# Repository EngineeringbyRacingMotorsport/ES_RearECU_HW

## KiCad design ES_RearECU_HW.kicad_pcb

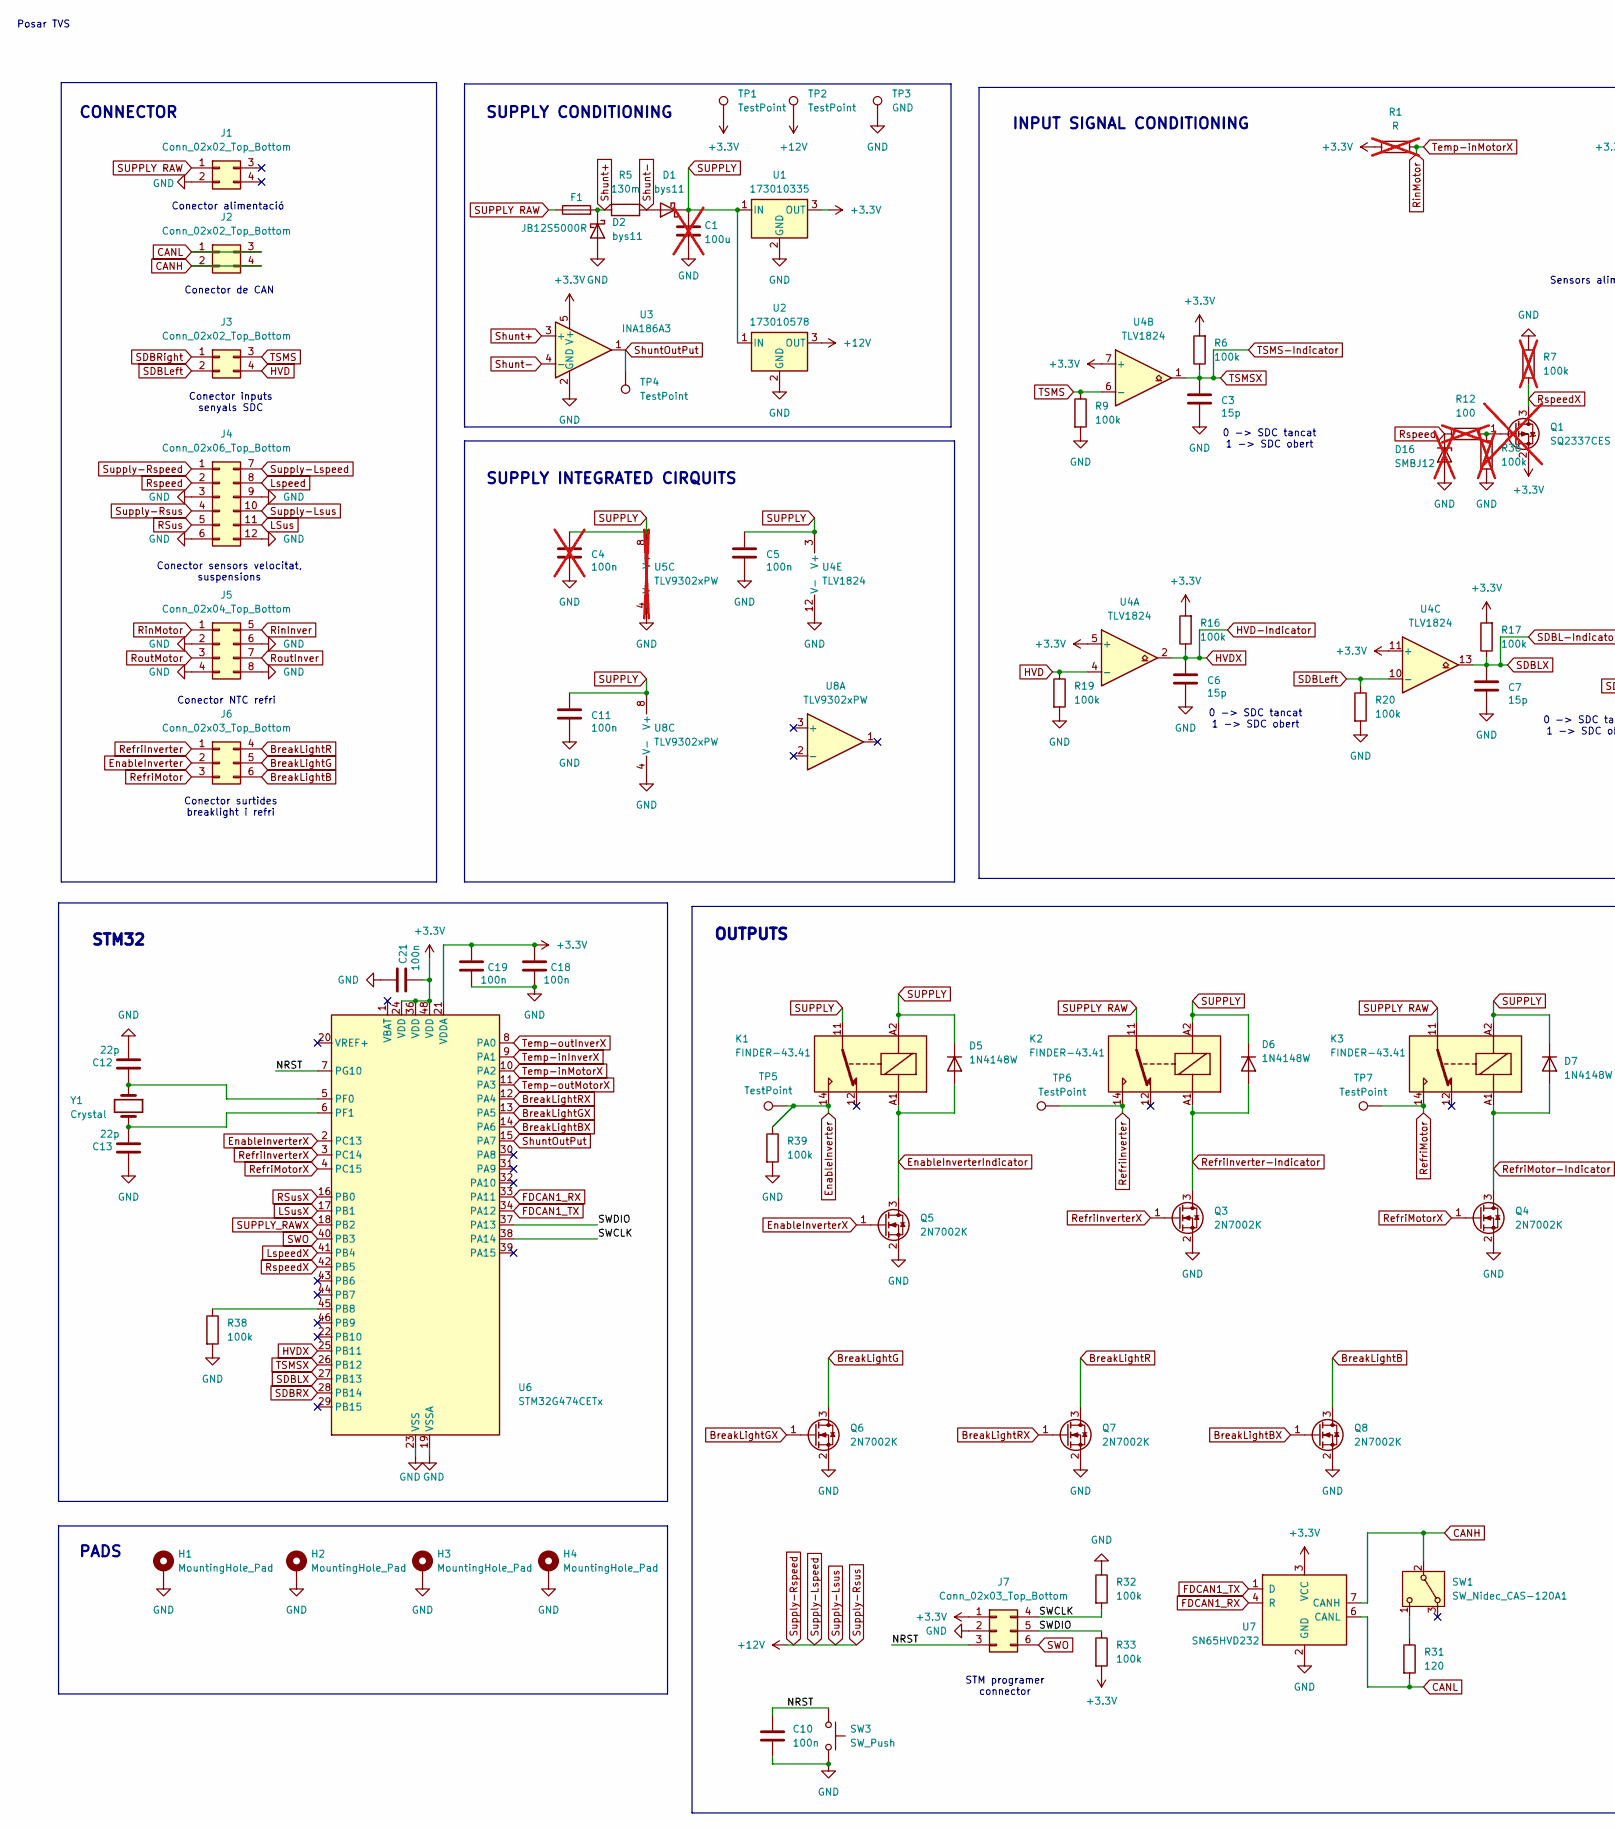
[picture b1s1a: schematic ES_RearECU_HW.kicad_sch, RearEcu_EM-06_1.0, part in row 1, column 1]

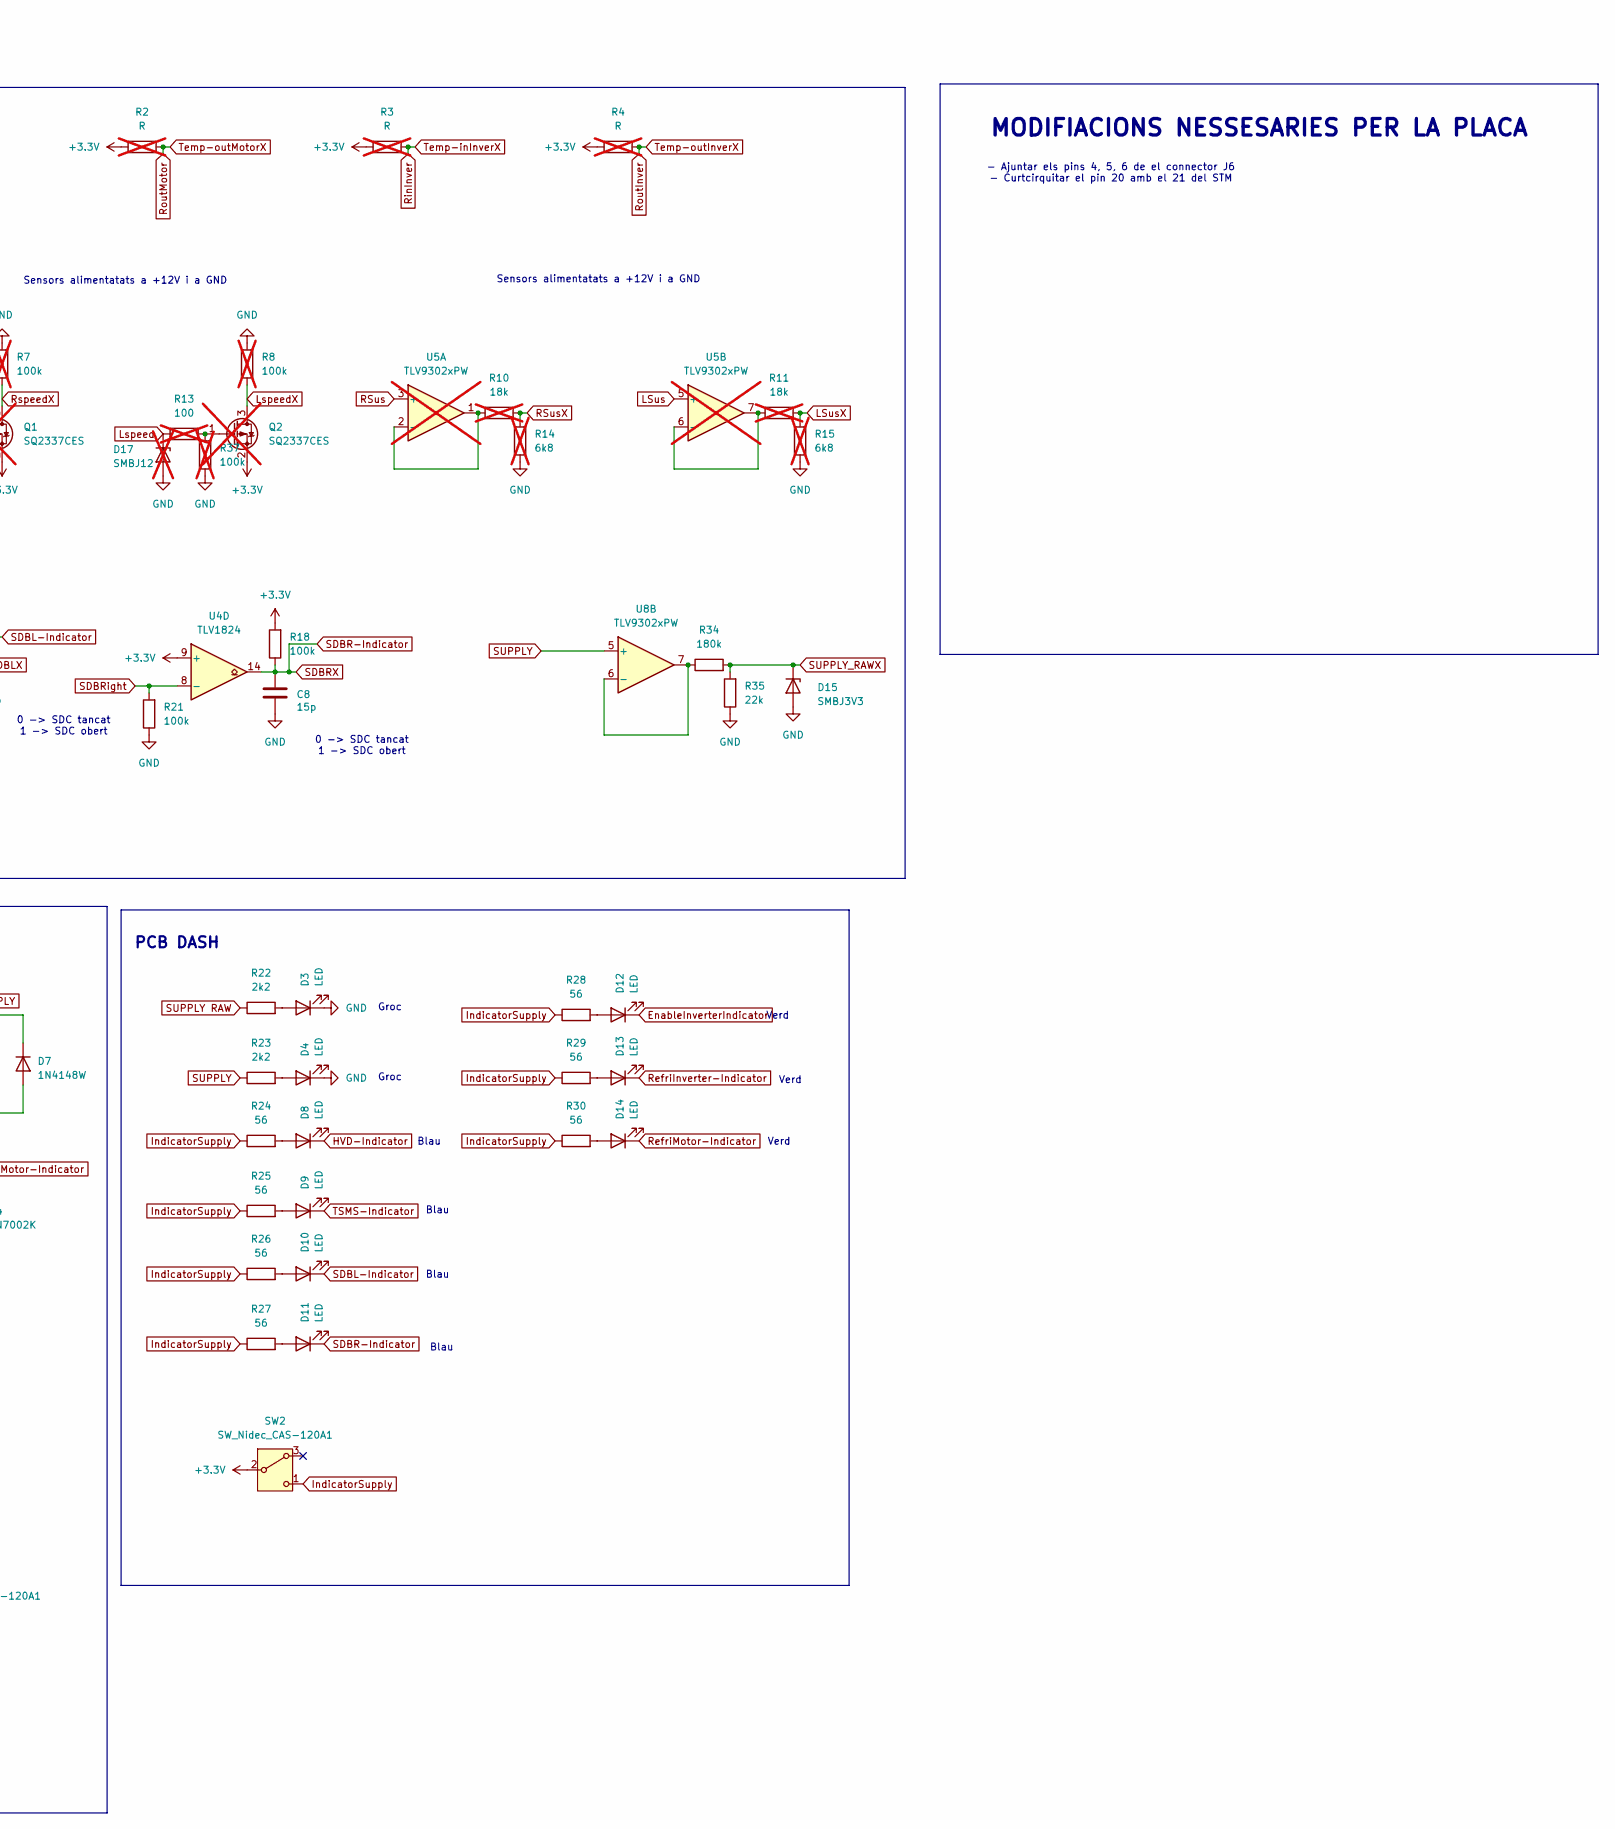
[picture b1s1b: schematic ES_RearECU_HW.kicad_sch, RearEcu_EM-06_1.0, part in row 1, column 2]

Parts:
C1: 100u; CP_Elec_10x10; not fitted
C3, C6, C7, C8: 15p; C_1206_3216Metric
C4: 100n; C_1206_3216Metric; not fitted
C5, C10, C11, C18, C19, C21: 100n; C_1206_3216Metric
C12, C13: 22p; C_1206_3216Metric
D1, D2: bys11; D_SMA
D3, D4, D8, D9, D10, D11, D12, D13, D14: LED; LED_0603_1608Metric
D5, D6, D7: 1N4148W; D_SOD-123
D15: SMBJ3V3; D_SMB
D16, D17: SMBJ12; D_SMB; not fitted
F1: JB12S5000R; Fuse_1206_3216Metric
H1, H2, H3, H4: MountingHole_Pad; MountingHole_3.5mm_Pad_Via
J1, J2, J3: Conn_02x02_Top_Bottom; Molex_Nano-Fit_105314-xx04_2x02_P2.50mm_Horizontal
J4: Conn_02x06_Top_Bottom; Molex_Nano-Fit_105314-xx12_2x06_P2.50mm_Horizontal
J5: Conn_02x04_Top_Bottom; Molex_Nano-Fit_105314-xx08_2x04_P2.50mm_Horizontal
J6: Conn_02x03_Top_Bottom; Molex_Nano-Fit_105314-xx06_2x03_P2.50mm_Horizontal
J7: Conn_02x03_Top_Bottom; Molex_Nano-Fit_105310-xx06_2x03_P2.50mm_Vertical
K1, K2, K3: FINDER-43.41; FINDER434170242001
Q1, Q2: SQ2337CES; SOT-23; not fitted
Q3, Q4, Q5, Q6, Q7, Q8: 2N7002K; SOT-23
R1, R2, R3, R4: R; R_1206_3216Metric; not fitted
R5: 130m; R_1206_3216Metric
R6, R9, R16, R17, R18, R19, R20, R21, R32, R33, R38, R39: 100k; R_1206_3216Metric
R7, R8, R36, R37: 100k; R_1206_3216Metric; not fitted
R10, R11: 18k; R_1206_3216Metric; not fitted
R12, R13: 100; R_1206_3216Metric; not fitted
R14, R15: 6k8; R_1206_3216Metric; not fitted
R22, R23: 2k2; R_1206_3216Metric
R24, R25, R26, R27, R28, R29, R30: 56; R_1206_3216Metric
R31: 120; R_1206_3216Metric
R34: 180k; R_1206_3216Metric
R35: 22k; R_1206_3216Metric
SW1, SW2: SW_Nidec_CAS-120A1; Nidec_Copal_CAS-120A
SW3: SW_Push; SW_Tactile_Straight_KSA0Axx1LFTR
TP1, TP2, TP4, TP5, TP6, TP7: TestPoint; TestPoint_Pad_D1.0mm
TP3: GND; TestPoint_Pad_D1.0mm
U1: 173010335; Converter_DCDC_RECOM_R-78E-0.5_THT
U2: 173010578; Converter_DCDC_RECOM_R-78E-0.5_THT
U3: INA186A3; SOT-23-5
U4: TLV1824; TSSOP-14_4.4x5mm_P0.65mm
U5: TLV9302xPW; TSSOP-8_4.4x3mm_P0.65mm; not fitted
U6: STM32G474CETx; LQFP-48_7x7mm_P0.5mm
U7: SN65HVD232; SOIC-8_3.9x4.9mm_P1.27mm
U8: TLV9302xPW; TSSOP-8_4.4x3mm_P0.65mm
Y1: Crystal; Crystal_SMD_HC49-SD

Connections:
+3.3V: C18.1, C19.1, C21.2, J7.1, Q1.2 (S), Q2.2 (S), R1.1, R2.1, R3.1, R4.1, R6.2, R16.2, R17.2, R18.2, R33.2, SW2.2 (B), TP1.1, U1.3 (OUT), U3.5 (V+), U4.5 (+), U4.7 (+), U4.9 (+), U4.11 (+), U6.21 (VDDA), U6.24 (VDD), U6.36 (VDD), U6.48 (VDD), U7.3 (VCC)
/NRST: C10.1, J7.3, SW3.1, U6.7 (PG10)
/SWCLK: J7.4, R32.2, U6.38 (PA14)
/SWDIO: J7.5, R33.1, U6.37 (PA13)
BreakLightB: J6.6, Q8.3 (D)
BreakLightBX: Q8.1 (G), U6.14 (PA6)
BreakLightG: J6.5, Q6.3 (D)
BreakLightGX: Q6.1 (G), U6.13 (PA5)
BreakLightR: J6.4, Q7.3 (D)
BreakLightRX: Q7.1 (G), U6.12 (PA4)
CANH: J2.2, J2.4, SW1.2 (B), U7.7 (CANH)
CANL: J2.1, J2.3, R31.2, U7.6 (CANL)
EnableInverter: J6.2, K1.14, R39.1, TP5.1
EnableInverterIndicator: D5.2 (A), D12.1 (K), K1.A1, Q5.3 (D)
EnableInverterX: Q5.1 (G), U6.2 (PC13)
FDCAN1_RX: U6.33 (PA11), U7.4 (R)
FDCAN1_TX: U6.34 (PA12), U7.1 (D)
GND: C1.2, C3.2, C4.2, C5.2, C6.2, C7.2, C8.2, C10.2, C11.2, C12.2, C13.1, C18.2, C19.2, C21.1, D2.2 (A), D3.1 (K), D4.1 (K), D15.2 (A), D16.2 (A), D17.2 (A), H1.1, H2.1, H3.1, H4.1, J1.2, J4.3, J4.6, J4.9, J4.12, J5.2, J5.4, J5.6, J5.8, J7.2, Q3.2 (S), Q4.2 (S), Q5.2 (S), Q6.2 (S), Q7.2 (S), Q8.2 (S), R7.1, R8.1, R9.2, R14.1, R15.1, R19.2, R20.2, R21.1, R32.1, R35.1, R36.2, R37.2, R38.2, R39.2, SW3.2, TP3.1, U1.2 (GND), U2.2 (GND), U3.2 (GND), U4.12 (V-), U5.4 (V-), U6.19 (VSSA), U6.23 (VSS), U6.35 (VSS), U6.47 (VSS), U7.2 (GND), U8.4 (V-)
HVD: J3.4, R19.1, U4.4 (-)
HVD-Indicator: C6.1, D8.1 (K), R16.1, U4.2, U6.25 (PB11)
IndicatorSupply: R24.1, R25.1, R26.1, R27.1, R28.1, R29.1, R30.1, SW2.1 (C)
LSus: J4.11, U5.5 (+)
LSusX: R11.2, R15.2, U6.17 (PB1)
Lspeed: D17.1 (K), J4.8, R13.1
LspeedX: Q2.3 (D), R8.2, U6.41 (PB4)
unnamed: D3.2 (A), R22.2
unnamed: D4.2 (A), R23.2
unnamed: D8.2 (A), R24.2
unnamed: D9.2 (A), R25.2
unnamed: D10.2 (A), R26.2
unnamed: D11.2 (A), R27.2
unnamed: D12.2 (A), R28.2
unnamed: D13.2 (A), R29.2
unnamed: D14.2 (A), R30.2
unnamed: Q1.1 (G), R12.2, R36.1
unnamed: Q2.1 (G), R13.2, R37.1
unnamed: R31.1, SW1.1 (C)
unnamed: R10.1, U5.1, U5.2 (-)
unnamed: R11.1, U5.6 (-), U5.7
unnamed: R38.1, U6.45 (PB8)
unnamed: C12.1, U6.5 (PF0), Y1.1
unnamed: C13.2, U6.6 (PF1), Y1.2
unnamed: R34.1, U8.6 (-), U8.7
RSus: J4.5, U5.3 (+)
RSusX: R10.2, R14.2, U6.16 (PB0)
RefriInverter: J6.1, K2.14, TP6.1
RefriInverter-Indicator: D6.2 (A), D13.1 (K), K2.A1, Q3.3 (D)
RefriInverterX: Q3.1 (G), U6.3 (PC14)
RefriMotor: J6.3, K3.14, TP7.1
RefriMotor-Indicator: D7.2 (A), D14.1 (K), K3.A1, Q4.3 (D)
RefriMotorX: Q4.1 (G), U6.4 (PC15)
RinInver: J5.5, R3.2, U6.9 (PA1)
RinMotor: J5.1, R1.2, U6.10 (PA2)
RoutInver: J5.7, R4.2, U6.8 (PA0)
RoutMotor: J5.3, R2.2, U6.11 (PA3)
Rspeed: D16.1 (K), J4.2, R12.1
RspeedX: Q1.3 (D), R7.2, U6.42 (PB5)
SDBL-Indicator: C7.1, D10.1 (K), R17.1, U4.13, U6.27 (PB13)
SDBLeft: J3.2, R20.1, U4.10 (-)
SDBR-Indicator: C8.1, D11.1 (K), R18.1, U4.14, U6.28 (PB14)
SDBRight: J3.1, R21.2, U4.8 (-)
SUPPLY: C1.1, C4.1, C5.1, C11.1, D1.1 (K), D5.1 (K), D6.1 (K), D7.1 (K), K1.11, K1.A2, K2.A2, K3.A2, R23.1, U1.1 (IN), U2.1 (IN), U4.3 (V+), U5.8 (V+), U8.5 (+), U8.8 (V+)
SUPPLY RAW: F1.1, J1.1, K2.11, K3.11, R22.1
SUPPLY_RAWX: D15.1 (K), R34.2, R35.2, U6.18 (PB2)
SWO: J7.6, U6.40 (PB3)
Shunt+: D2.1 (K), F1.2, R5.1, U3.3 (+)
Shunt-: D1.2 (A), R5.2, U3.4 (-)
ShuntOutPut: TP4.1, U3.1, U6.15 (PA7)
Supply-Lspeed: J4.1, J4.4, J4.7, J4.10, TP2.1, U2.3 (OUT)
TSMS: J3.3, R9.1, U4.6 (-)
TSMS-Indicator: C3.1, D9.1 (K), R6.1, U4.1, U6.26 (PB12)

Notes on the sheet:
STM programer connector
- Ajuntar els pins 4, 5, 6 de el connector J6 - Curtcirquitar el pin 20 amb el 21 del STM
Posar TVS
Conector NTC refri
Blau
0 -> SDC tancat 1 -> SDC obert
Groc
Blau
SUPPLY INTEGRATED CIRQUITS
Conector de CAN
MODIFIACIONS NESSESARIES PER LA PLACA
0 -> SDC tancat 1 -> SDC obert
SUPPLY CONDITIONING
Conector inputs senyals SDC
INPUT SIGNAL CONDITIONING
Sensors alimentatats a +12V i a GND
Conector surtides breaklight i refri
STM32
PCB DASH
Verd
CONNECTOR
OUTPUTS
PADS
Conector sensors velocitat, suspensions
Conector alimentació

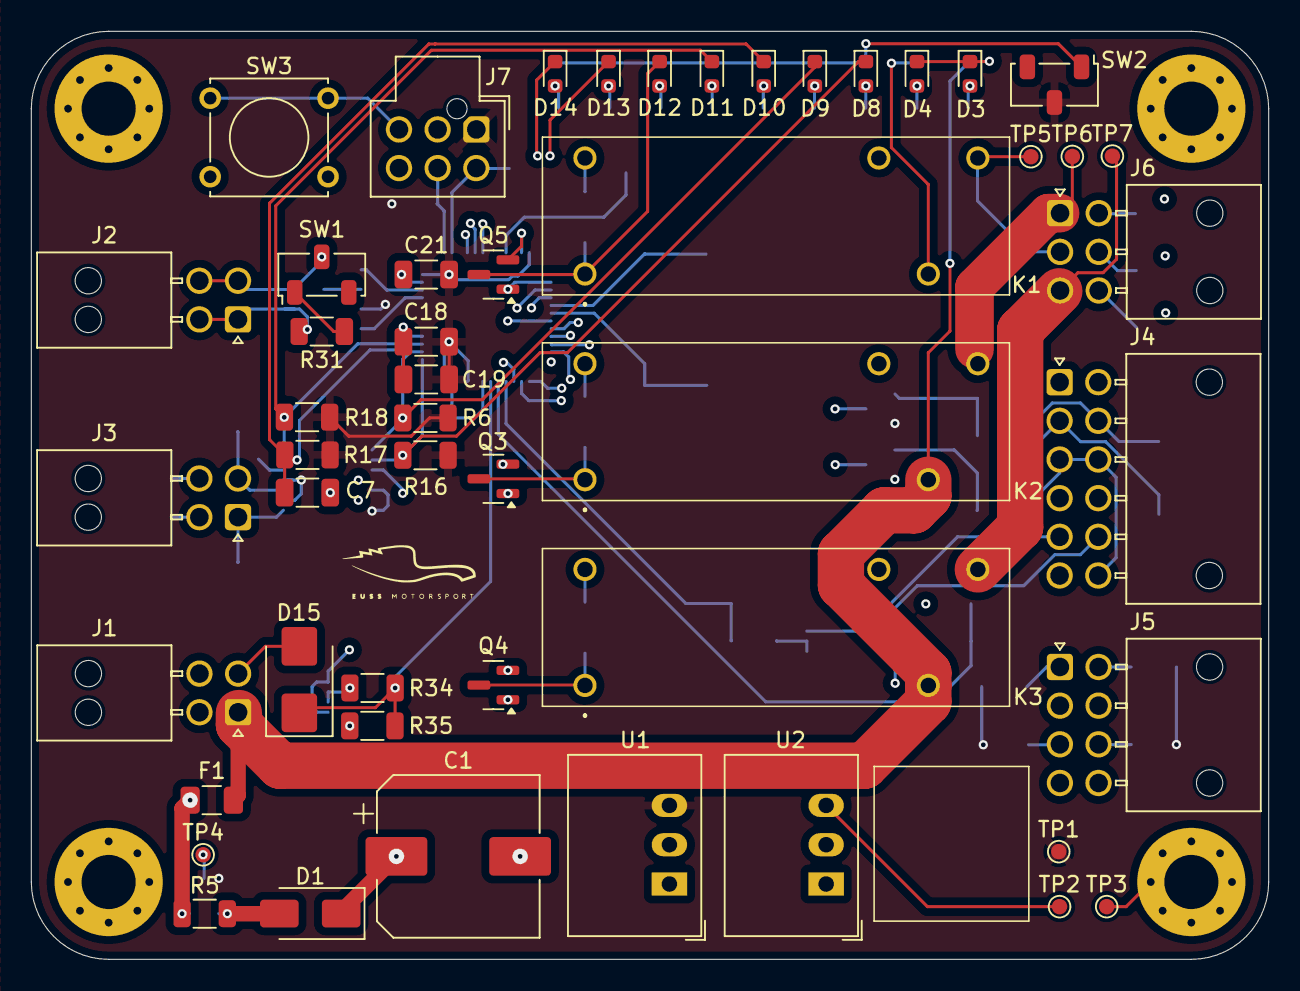
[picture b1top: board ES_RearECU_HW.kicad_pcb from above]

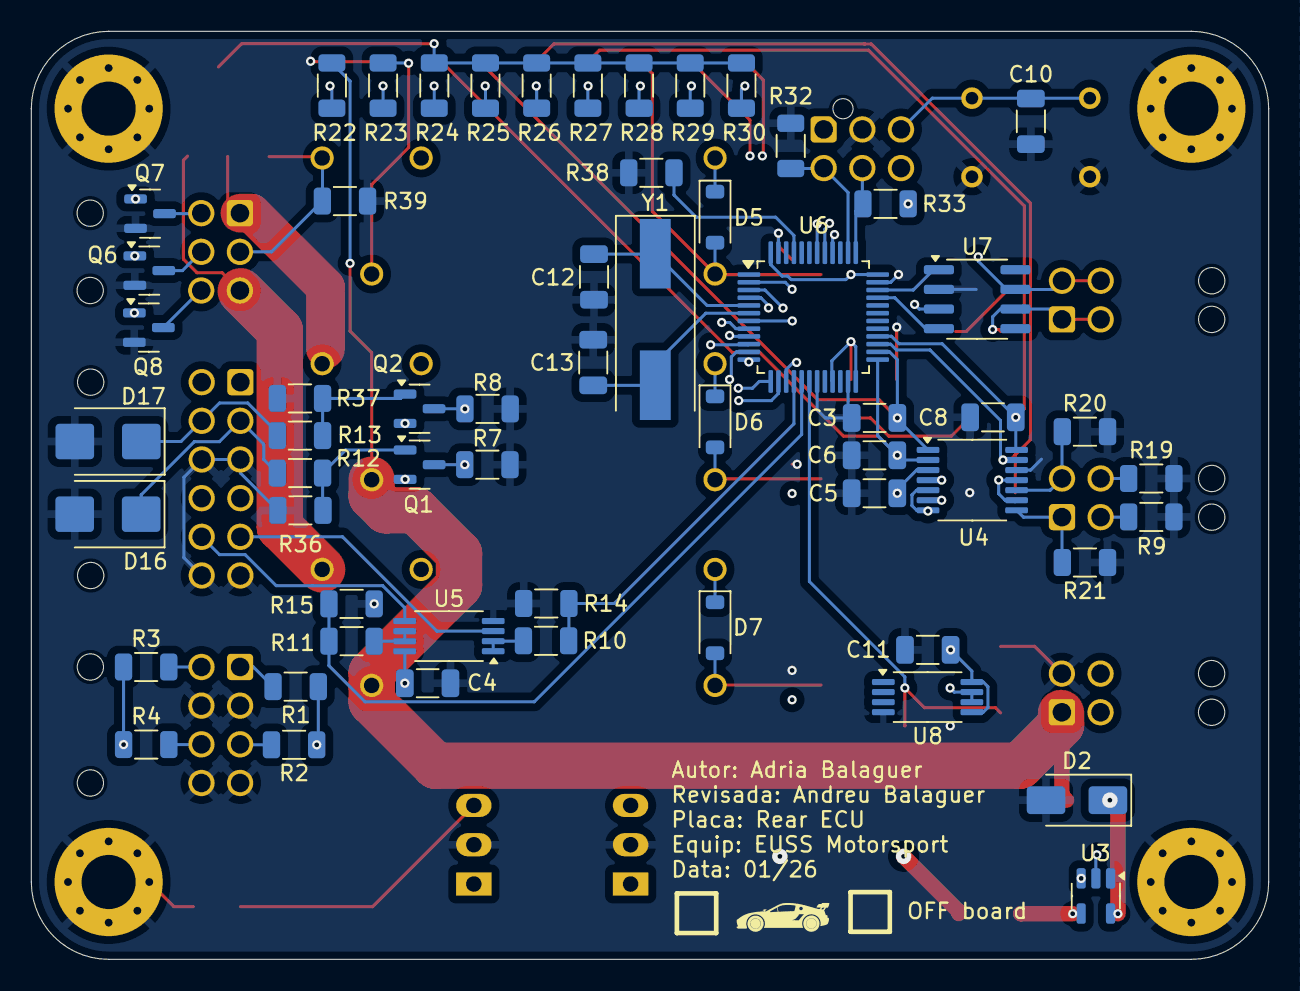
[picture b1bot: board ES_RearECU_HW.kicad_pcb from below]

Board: 4 copper layers, 80.0 x 60.0 mm, 112 parts (58 on the bottom side), 71 nets.
